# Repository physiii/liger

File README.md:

# ESP32 Room Sensor

## Schematic Overview

## Motion (PIR) Component

## Features
Motion detection<br>
Audio detection<br>
Media control<br>
Security mode<br>
Light level<br>

## Sensor components
I2S Microphone<br>
Speaker<br>
IR Transmitter<br>
IR Receiver<br>
directional soft button<br>
I2C luminosity<br>
Dual PIR for animal vs human distrinction<br>
Ultrasonic (optional)<br>
Temperature/Humidity<br>

## Applications
Building Automation<br>
Motion Detection<br>
Intrusion Detection<br>
Occupancy Detector<br>
Room Monitors<br>
Pet Detection<br>
Fire Detection<br>
Falling Person Detection<br>

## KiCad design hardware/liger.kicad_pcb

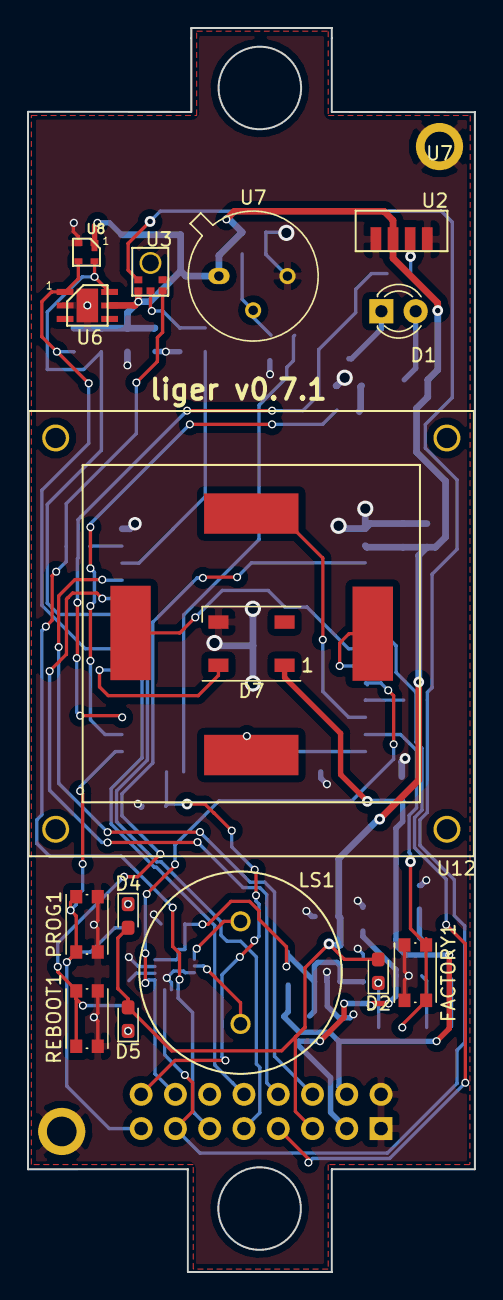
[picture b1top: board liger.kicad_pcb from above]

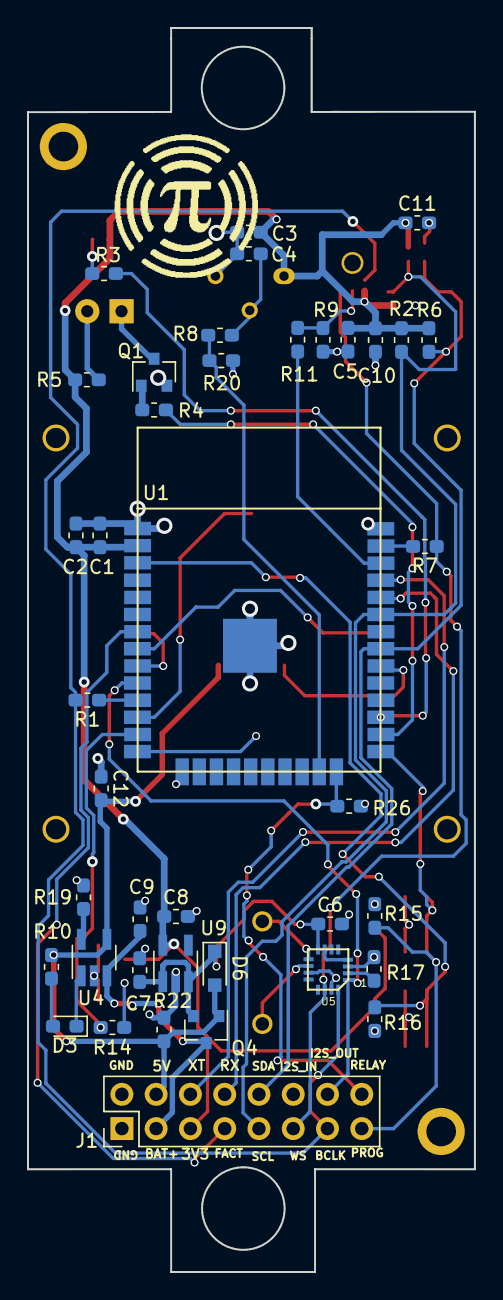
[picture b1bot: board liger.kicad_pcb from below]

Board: 2 copper layers, 33.1 x 92.2 mm, 57 parts (41 on the bottom side), 43 nets.

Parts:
C1: C_10uF; C_0603_1608Metric_Pad1.05x0.95mm_HandSolder
C2, C7, C8, C9, C12: C_1uF; C_0603_1608Metric_Pad1.05x0.95mm_HandSolder
C3, C5, C6, C10, C11: C_0.1uF; C_0603_1608Metric_Pad1.05x0.95mm_HandSolder
C4: C_100pF; C_0603_1608Metric_Pad1.05x0.95mm_HandSolder
D1: LED; LED_D3.0mm
D2, D3, D4, D5: LED-0603-G; LED_0603_1608Metric_Pad1.05x0.95mm_HandSolder
D6: D_Schottky-BAT20JFILM; D_SOD-323_HandSoldering
D7: WS2812B; LED_WS2812B_PLCC4_5.0x5.0mm_P3.2mm
FACTORY1: SW_PUSH; SW_SPST_KMR2
J1: Conn_02x08_Odd_Even; PinHeader_2x08_P2.54mm_Vertical
LOGO: pyfi_symbol
LS1: speaker-CVS-1508; speaker-1508
PROG1: SW_PUSH; SW_SPST_KMR2
Q1: Q_NPN_BEC; SOT-23
Q4: PMOS-DMG3413L; SOT-23
R1, R7, R8, R11: R_47.5; R_0603_1608Metric_Pad1.05x0.95mm_HandSolder
R2, R6, R22, R26: R_10k; R_0603_1608Metric_Pad1.05x0.95mm_HandSolder
R3, R4, R10, R14, R15, R16: R_1k; R_0603_1608Metric_Pad1.05x0.95mm_HandSolder
R5: 36; R_0603_1608Metric_Pad1.05x0.95mm_HandSolder
R9, R17, R20: R_100k; R_0603_1608Metric_Pad1.05x0.95mm_HandSolder
R19: R_2k; R_0603_1608Metric_Pad1.05x0.95mm_HandSolder
REBOOT1: SW_PUSH; SW_SPST_KMR2
U1: ESP-WROOM-32
U2: IR-RX-TSOP34438; TSOP75338TR
U3: SPH0645LM4H-B
U4: MCP73831T; SOT-23-5_HandSoldering
U5: MAX98357AETE+T; MAX98357A
U6: SI7020-A20
U7: housing-mounts; generic-housing-mounts-md
U7#2: PYQ2898; TO-5-3
U8: TSL45315CL; LIGHT-SENSOR-TSL45315CL
U9: AP2112; SOT-23-5_HandSoldering
U12: soft-button-4x; soft-button-4

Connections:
/3V3: C1.1, C2.1, C3.1, C5.1, C8.1, C10.1, C11.1, D2.2, D4.2, D5.2, J1.5, R2.1, R5.1, R6.1, U1.2, U2.Vs, U3.5, U6.5, U7#2.1, U8.1, U9.5
/BUTTON_LED: D7.4, U1.30
/EN: R16.2, REBOOT1.1, U1.3
/FACTORY_RST: FACTORY1.1, R14.2, U1.13
/I2S_BCLK: J1.13, R1.2, U3.4, U5.16
/I2S_DATA_IN: R11.1, U1.36
/I2S_DATA_OUT: J1.14, U1.10, U5.1
/I2S_WS: J1.11, R7.1, U3.1, U5.14
/IR_RX: R3.1, U1.27
/IR_TX: R4.2, U1.26
/PIR: R8.1, R20.2, U1.23
/PROG: J1.15, PROG1.1, R15.2, U1.25
/RELAY: J1.16, R26.1, U1.24
/RXD: J1.8, U1.34
/SCL: J1.9, R2.2, U1.33, U6.6, U8.4
/SDA: J1.10, R6.2, U1.31, U6.1, U8.3
/TXD: J1.6, U1.35
/T_DOWN: U1.14, U12.4
/T_LEFT: U1.8, U12.1
/T_RIGHT: U1.9, U12.2
/T_UP: U1.12, U12.3
/V_BAT: C9.1, J1.3, Q4.3, U4.3
/V_IN: C6.1, C7.1, D6.1, Q4.2, U5.4, U5.7, U9.1, U9.3
/V_USB: C12.2, D6.2, D7.1, J1.4, Q4.1, R10.1, R22.1, U4.4
/ZERO_DETECT: J1.7, U1.7
GND: C1.2, C2.2, C3.2, C4.2, C5.2, C6.2, C7.2, C8.2, C9.2, C10.2, C11.2, C12.1, D7.3, FACTORY1.2, J1.1, J1.2, PROG1.2, Q1.2, R9.1, R17.2, R19.1, R20.1, R22.2, R26.2, REBOOT1.2, U1.1, U2.GND, U3.2, U3.3, U4.2, U5.3, U6.2, U7.1, U7#2.3, U8.2, U9.2
unnamed: C4.1, R8.2, U7#2.2
unnamed: D1.1, Q1.3
unnamed: D1.2, R5.2
unnamed: D2.1, R14.1
unnamed: D3.1, U4.1
unnamed: D3.2, R10.2
unnamed: D4.1, R15.1
unnamed: D5.1, R16.1
unnamed: LS1.1, U5.10
unnamed: LS1.2, U5.9
unnamed: Q1.1, R4.1
unnamed: R1.1, U1.11
unnamed: R3.2, U2.OUT
unnamed: R7.2, U1.37
unnamed: R9.2, R11.2, U3.6
unnamed: R17.1, U5.2
unnamed: R19.2, U4.5

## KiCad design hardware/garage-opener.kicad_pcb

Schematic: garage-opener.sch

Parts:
C1, C2: 1uf; C_0603; Part Number VJ0805G106KXQTW1BC
C3: 0.1uf; C_0603; Part Number VJ0805G106KXQTW1BC
C4: 4.7uf; C_0603; Part Number KEM_C1002_X7R_SMD-357932
C5, C6: 47pF; C_0603; Part Number VJ0603A470JXACW1BC
C7: 100nF; C_0603; Part Number VJ0603A470JXACW1BC
D1, D4, D7, D8, D9: LED; LED_0805; Part Number LS Q976-NR-1
D2: ZENER; SOD-123; Part Number MBR120VLSFT1G
D5, D6: SS14; SMA_Standard; Part Number SS14
FB1: BK0603HS330-T; R_0603; Part Number BK0603HS330-T
JP1: CONN_01X06; Pin_Header_Straight_1x06
JP2, JP3: CONN_01X10; Pin_Header_Straight_1x10
JP4: CONN_01X04; Pin_Header_Angled_1x04
P1: USB_OTG; USB_Micro-B; Part Number 10118194-0001LF
P2: 1935161; bornier2; Part Number ESPM02200
Q1: MMBT3904LT1G; SOT-23; Part Number MMBT3904LT1G
Q2: 2N7002L; SOT-23; Part Number 2N7002L
Q3: BSS84LT1G; SOT-23; Part Number BSS84LT1G
R1, R2, R4, R6, R7, R8, R9, R12, R13, R14, R15, R16: 1K; R_0603; Part Number ERJ-1GE0R00C
R3, R5: 10K; R_0603; Part Number ERJ-1GE0R00C
R10, R11: 27K; R_0603; Part Number ERJ-1GE0R00C
RL1: 833H-1C-S-5VDC; 883H; Part Number 893-833H-1C-S-5VDC
SW2: SW_PUSH; SW_SPST_KMR2; Part Number KMR211NG LFS
U1: ESP-WROOM-02; Part Number ESP-WROOM-02
U2: FT230XS; SSOP-16_3.9x4.9mm_Pitch0.635mm; Part Number FT230XS
U11: SPX3819; SOT-23-5; Part Number SPX3819

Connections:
+3V3: C2.2, C3.2, D1.2 (A), D4.2 (A), FB1.1, JP2.10, R1.1, R5.2, U1.1, U11.5
+5V: D2.2, JP1.4, JP3.8, P1.1; also elsewhere on the board
+BATT: JP3.9
ADC: JP3.2, U1.16
CH_PD: JP2.9, R5.1, U1.2
DM: C5.1, P1.2, R10.2
DP: C6.1, P1.3, R11.2
GND: C1.2, C2.1, C3.1, C4.2, C5.2, C6.2, C7.2, D6.2, JP1.6, JP2.1, JP2.2, JP3.10, P1.5, P1.6, Q1.2, Q2.2, R2.2, R3.2, SW2.2, U1.9, U1.13, U1.18, U2.5, U2.13, U11.2, U11.3; also elsewhere on the board
IO0: JP2.3, R9.1, U1.8
IO2: JP2.4, R1.2, U1.7
IO4: JP3.7, U1.10
IO5: JP3.4, R8.2, U1.14
IO12: JP2.7, U1.4; also elsewhere on the board
IO13: JP2.6
IO14: D6.1, JP2.8, R4.2, U1.3
IO15: JP2.5, R2.1, R13.1, U1.6
IO16: JP3.1, U1.17
unnamed: C1.1, D2.1, R3.1, U11.1
unnamed: C4.1, Q2.1, R6.2
unnamed: C7.1, D7.2 (A), D8.2 (A), D9.2 (A), U2.3, U2.10, U2.11
unnamed: D1.1 (K), Q3.2, R7.1
unnamed: D4.1 (K), R8.1
unnamed: D5.1, RL1.A1
unnamed: D5.2, Q1.3, RL1.A2
unnamed: D7.1 (K), R12.1
unnamed: D8.1 (K), R14.1
unnamed: D9.1 (K), R16.1
unnamed: FB1.2, U2.12
unnamed: P2.1, RL1.14
unnamed: P2.2, RL1.11
unnamed 33: R4.1; also elsewhere on the board
unnamed: Q1.1, R13.2
unnamed: Q2.3, R9.2
unnamed: Q3.3, R6.1
unnamed: R10.1, U2.9
unnamed: R11.1, U2.8
unnamed: R12.2, U2.15
unnamed: R14.2, U2.14
unnamed: R15.2, U2.7
unnamed: R16.2, U2.16
RESET: JP3.3, Q3.1, R7.2, R15.1, SW2.1, U1.15
RXD: JP3.6, U1.11, U2.1
RXD_5V: JP1.3
TXD: JP1.2, JP3.5, U1.12, U2.4

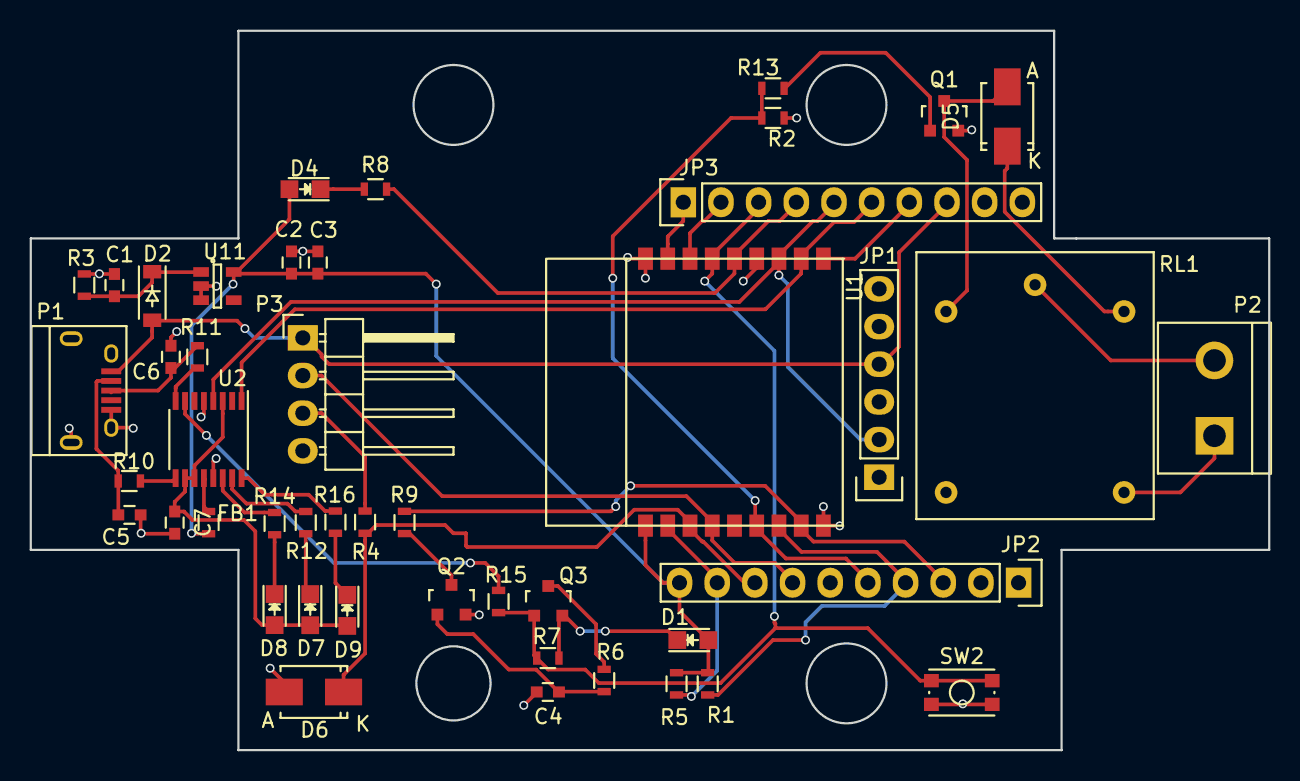
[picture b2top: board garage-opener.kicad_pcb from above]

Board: 2 copper layers, 83.5 x 48.5 mm, 46 parts (0 on the bottom side), 41 nets.

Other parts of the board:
P3: CONN_01X04; Pin_Header_Angled_1x04

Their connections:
+5V: P3.1; also elsewhere on the board
GND: P3.4; also elsewhere on the board
IO12: P3.2; also elsewhere on the board
unnamed 33: P3.3; also elsewhere on the board

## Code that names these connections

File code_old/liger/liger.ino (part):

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WebSocketsClient webSocket;
#define TRIGGER 12
#define ECHO    14
#define RELAY   15
#define MIC     A0
#define PIR     16
#define IR_RX   4
#define IR_TX   14
#define SW      13
#define SW_LED  5
 
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/** the current address in the EEPROM (i.e. which byte we're going to write to next) **/
int addr = 0;
const char *ap_ssid = "room_sensor ";
const char *io_relay = "192.168.0.2";
const char *version_number = "room_sensor_v0.1";
int io_port = 4000;
//const char *ap_password = "password";
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void setup() {
  Serial.begin(115200);
  EEPROM.begin(512);
  pinMode(PIR, INPUT);
  pinMode(ECHO, INPUT);
  pinMode(SW, INPUT);
  pinMode(SW_LED, OUTPUT);
  pinMode(TRIGGER, OUTPUT);
  pinMode(RELAY, OUTPUT);
  irrecv.enableIRIn(); // Start the receiver
  irsend.begin();
  getmac();
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
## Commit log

2016-06-17 liger
2016-06-20 liger .2
2016-06-20 liger 0.2
2016-06-25 more datasheets
2016-06-25 all current data sheets are done
2016-06-27 pcb bitches
2016-06-30 pcb1
2016-06-30 pcbebe
2016-07-01 almost done
2016-07-03 last push
2016-07-07 errything
2016-07-20 final update
2016-07-25 fixed footprint errors, reorganized
2016-08-27 just Checking
2016-09-06 yupdate
2016-09-07 added MEMS mic
2016-11-15 sync.sh update
2017-08-07 updatge
2017-09-15 update:
2018-06-12 updated schematic
2018-06-12 added interface
2018-08-01 testing new ws code
2018-08-01 multifile update
2018-08-03 added http request headers
2018-08-03 added autoreconnect when disconnected from ws server
2018-08-03 replacing default token with token from server
2018-08-04 added autoreconnect with new rotken
2018-08-06 token exchange system with relay
2018-08-06 fixed storing token
2018-08-06 adding motion service
2018-08-08 added dpad
2018-08-09 finishing up buttons, json error checking
2018-08-10 worked on websocket connection
2018-08-10 json checking
2018-08-14 added physical button to switch function
2018-08-14 added device type "liger" to http headers
2018-08-14 added toggle function
2018-08-14 fixed button service conflict
2018-08-15 fixed crash in switch service
2018-08-16 refactor
2018-08-20 working PYQ2898 demo
2018-08-22 layout complete
2018-08-22 corrections
2018-08-22 ws2812b
2018-08-22 pcb complete
2018-08-22 final touches on silkscreen, sending off to oshpark
2018-08-22 add bom
2018-08-23 order complete
2018-08-26 adding binary switch driver for magnetic switch
2018-08-28 binary switch driver
2018-08-29 added contact switch driver and service
2018-08-30 siren test
2018-09-02 track these
2018-09-02 broken timer code
2018-09-13 change touch to use interrupt
2018-09-14 using exponential moving average to calc pir values
2018-09-14 added ssl connection
2018-09-16 adding ssl
2018-09-16 created motion service that uses PIR driver
2018-09-16 updated load message
2018-09-22 fixed id bug
2018-09-22 testing pir
2018-09-28 update schematic
2018-10-07 update button
2018-10-21 update model
2018-10-24 0.7.1
2018-10-28 added dimmer
2018-10-28 clean up
2018-11-02 starting event schedular
2018-11-02 starting event scheduler
2018-11-05 added schedule service
2018-11-06 Added new Liger Model
2018-11-07 add scheduler
2018-11-07 updated stl for liger model
2018-11-08 shortened model from 20mm to 10mm height. stl updated as well
2018-11-09 fixing schedule bugs
2018-11-10 schedule feature tested
2018-11-14 testing scheduler/dimmer
2018-11-23 get uuid from utility server
2018-11-28 working on PIR calibration
2018-11-28 send board to board house, v0.7.2
2018-12-03 reconfigured touch for silicon button
2018-12-07 detect average motion value and use that to set thresholds
2018-12-07 debounce pir when changing lights
2018-12-09 Bad Y-axis model
2018-12-26 tuning pir
2018-12-28 more pir tuning, fixed dimmer fade issue
2018-12-31 changed pir detection method, made new model
2018-12-31 model changes
2019-01-01 model update
2019-01-02 rounded edges, slotted for button, added wall tabs
2019-01-09 updated model
2019-01-17 starting audio service
2019-01-21 added microphone service
2019-01-22 increased width for lens
2019-01-26 dimmer fix
2019-02-16 fixed autoconnect and schedule bugs
2019-02-20 finishing microphone driver and service
2019-02-20 added payload for motion and audio alarm thresholds
2019-03-02 added thresholds for motion, microphone, and touch. Added storage_in_use flag to prevent crash
2019-03-09 Cleaning up, motion triggers light on
2019-04-02 redoing model
2019-07-08 changing motion drivers
2020-09-04 Bump mongodb from 2.2.36 to 3.1.13 in /code/server
    Bumps [mongodb](https://github.com/mongodb/node-mongodb-native) from 2.2.36 to 3.1.13.
    - [Release notes](https://github.com/mongodb/node-mongodb-native/releases)
    - [Changelog](https://github.com/mongodb/node-mongodb-native/blob/master/CHANGES_3.0.0.md)
    - [Commits](https://github.com/mongodb/node-mongodb-native/compare/v2.2.36...v3.1.13)
2020-09-06 Bump http-proxy from 1.17.0 to 1.18.1 in /code/server
    Bumps [http-proxy](https://github.com/http-party/node-http-proxy) from 1.17.0 to 1.18.1.
    - [Release notes](https://github.com/http-party/node-http-proxy/releases)
    - [Changelog](https://github.com/http-party/node-http-proxy/blob/master/CHANGELOG.md)
    - [Commits](https://github.com/http-party/node-http-proxy/compare/1.17.0...1.18.1)
2021-01-21 Bump socket.io from 2.1.1 to 2.4.0 in /code/server
    Bumps [socket.io](https://github.com/socketio/socket.io) from 2.1.1 to 2.4.0.
    - [Release notes](https://github.com/socketio/socket.io/releases)
    - [Changelog](https://github.com/socketio/socket.io/blob/2.4.0/CHANGELOG.md)
    - [Commits](https://github.com/socketio/socket.io/compare/2.1.1...2.4.0)
2021-05-06 Bump underscore from 1.9.1 to 1.12.1 in /code/server
    Bumps [underscore](https://github.com/jashkenas/underscore) from 1.9.1 to 1.12.1.
    - [Release notes](https://github.com/jashkenas/underscore/releases)
    - [Commits](https://github.com/jashkenas/underscore/compare/1.9.1...1.12.1)
2021-05-12 Bump nodemailer from 4.6.7 to 6.4.16 in /code/server
    Bumps [nodemailer](https://github.com/nodemailer/nodemailer) from 4.6.7 to 6.4.16.
    - [Release notes](https://github.com/nodemailer/nodemailer/releases)
    - [Changelog](https://github.com/nodemailer/nodemailer/blob/master/CHANGELOG.md)
    - [Commits](https://github.com/nodemailer/nodemailer/compare/v4.6.7...v6.4.16)
2022-10-29 Bump socket.io-parser, socket.io and socket.io-client in /code/server
    Bumps [socket.io-parser](https://github.com/socketio/socket.io-parser) to 3.4.1 and updates ancestor dependencies [socket.io-parser](https://github.com/socketio/socket.io-parser), [socket.io](https:/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
    Updates `socket.io-parser` from 3.2.0 to 3.4.1
    - [Release notes](https://github.com/socketio/socket.io-parser/releases)
    - [Changelog](https://github.com/socketio/socket.io-parser/blob/main/CHANGELOG.md)
    - [Commits](https://github.com/socketio/socket.io-parser/compare/3.2.0...3.4
2022-11-10 Bump socket.io-parser, socket.io and socket.io-client in /code/server
    Bumps [socket.io-parser](https://github.com/socketio/socket.io-parser) to 3.4.2 and updates ancestor dependencies [socket.io-parser](https://github.com/socketio/socket.io-parser), [socket.io](https:/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
    Updates `socket.io-parser` from 3.2.0 to 3.4.2
    - [Release notes](https://github.com/socketio/socket.io-parser/releases)
    - [Changelog](https://github.com/socketio/socket.io-parser/blob/main/CHANGELOG.md)
    - [Commits](https://github.com/socketio/socket.io-parser/compare/3.2.0...3.4
2022-11-22 Bump engine.io and socket.io in /code/server
    Bumps [engine.io](https://github.com/socketio/engine.io) to 3.6.1 and updates ancestor dependency [socket.io](https://github.com/socketio/socket.io). These dependencies need to be updated together.
    Updates `engine.io` from 3.2.0 to 3.6.1
    - [Release notes](https://github.com/socketio/engine.io/releases)
    - [Changelog](https://github.com/socketio/engine.io/blob/main/CHANGELOG.md)
    - [Commits](https://github.com/socketio/engine.io/compare/3.2.0...3.6.1)
    Updates `socket.io` from 2.1.1 to 2.5.0
2022-12-07 Bump qs, body-parser and express in /code/server
    Bumps [qs](https://github.com/ljharb/qs) to 6.5.3 and updates ancestor dependencies [qs](https://github.com/ljharb/qs), [body-parser](https://github.com/expressjs/body-parser) and [express](https://g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
    Updates `qs` from 6.5.2 to 6.5.3
    - [Release notes](https://github.com/ljharb/qs/releases)
    - [Changelog](https://github.com/ljharb/qs/blob/main/CHANGELOG.md)
    - [Commits](https://github.com/ljharb/qs/compare/v6.5.2...v6.5.3)
    Updates `body-parser` from 1.18.3 to 1.20.1
2022-12-08 Bump express from 4.16.3 to 4.17.3 in /code/server
    Bumps [express](https://github.com/expressjs/express) from 4.16.3 to 4.17.3.
    - [Release notes](https://github.com/expressjs/express/releases)
    - [Changelog](https://github.com/expressjs/express/blob/master/History.md)
    - [Commits](https://github.com/expressjs/express/compare/4.16.3...4.17.3)
    ---
    updated-dependencies:

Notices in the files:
code_old/liger/liger.ino:
Copyright (c) 2015, Majenko Technologies
All rights reserved.
